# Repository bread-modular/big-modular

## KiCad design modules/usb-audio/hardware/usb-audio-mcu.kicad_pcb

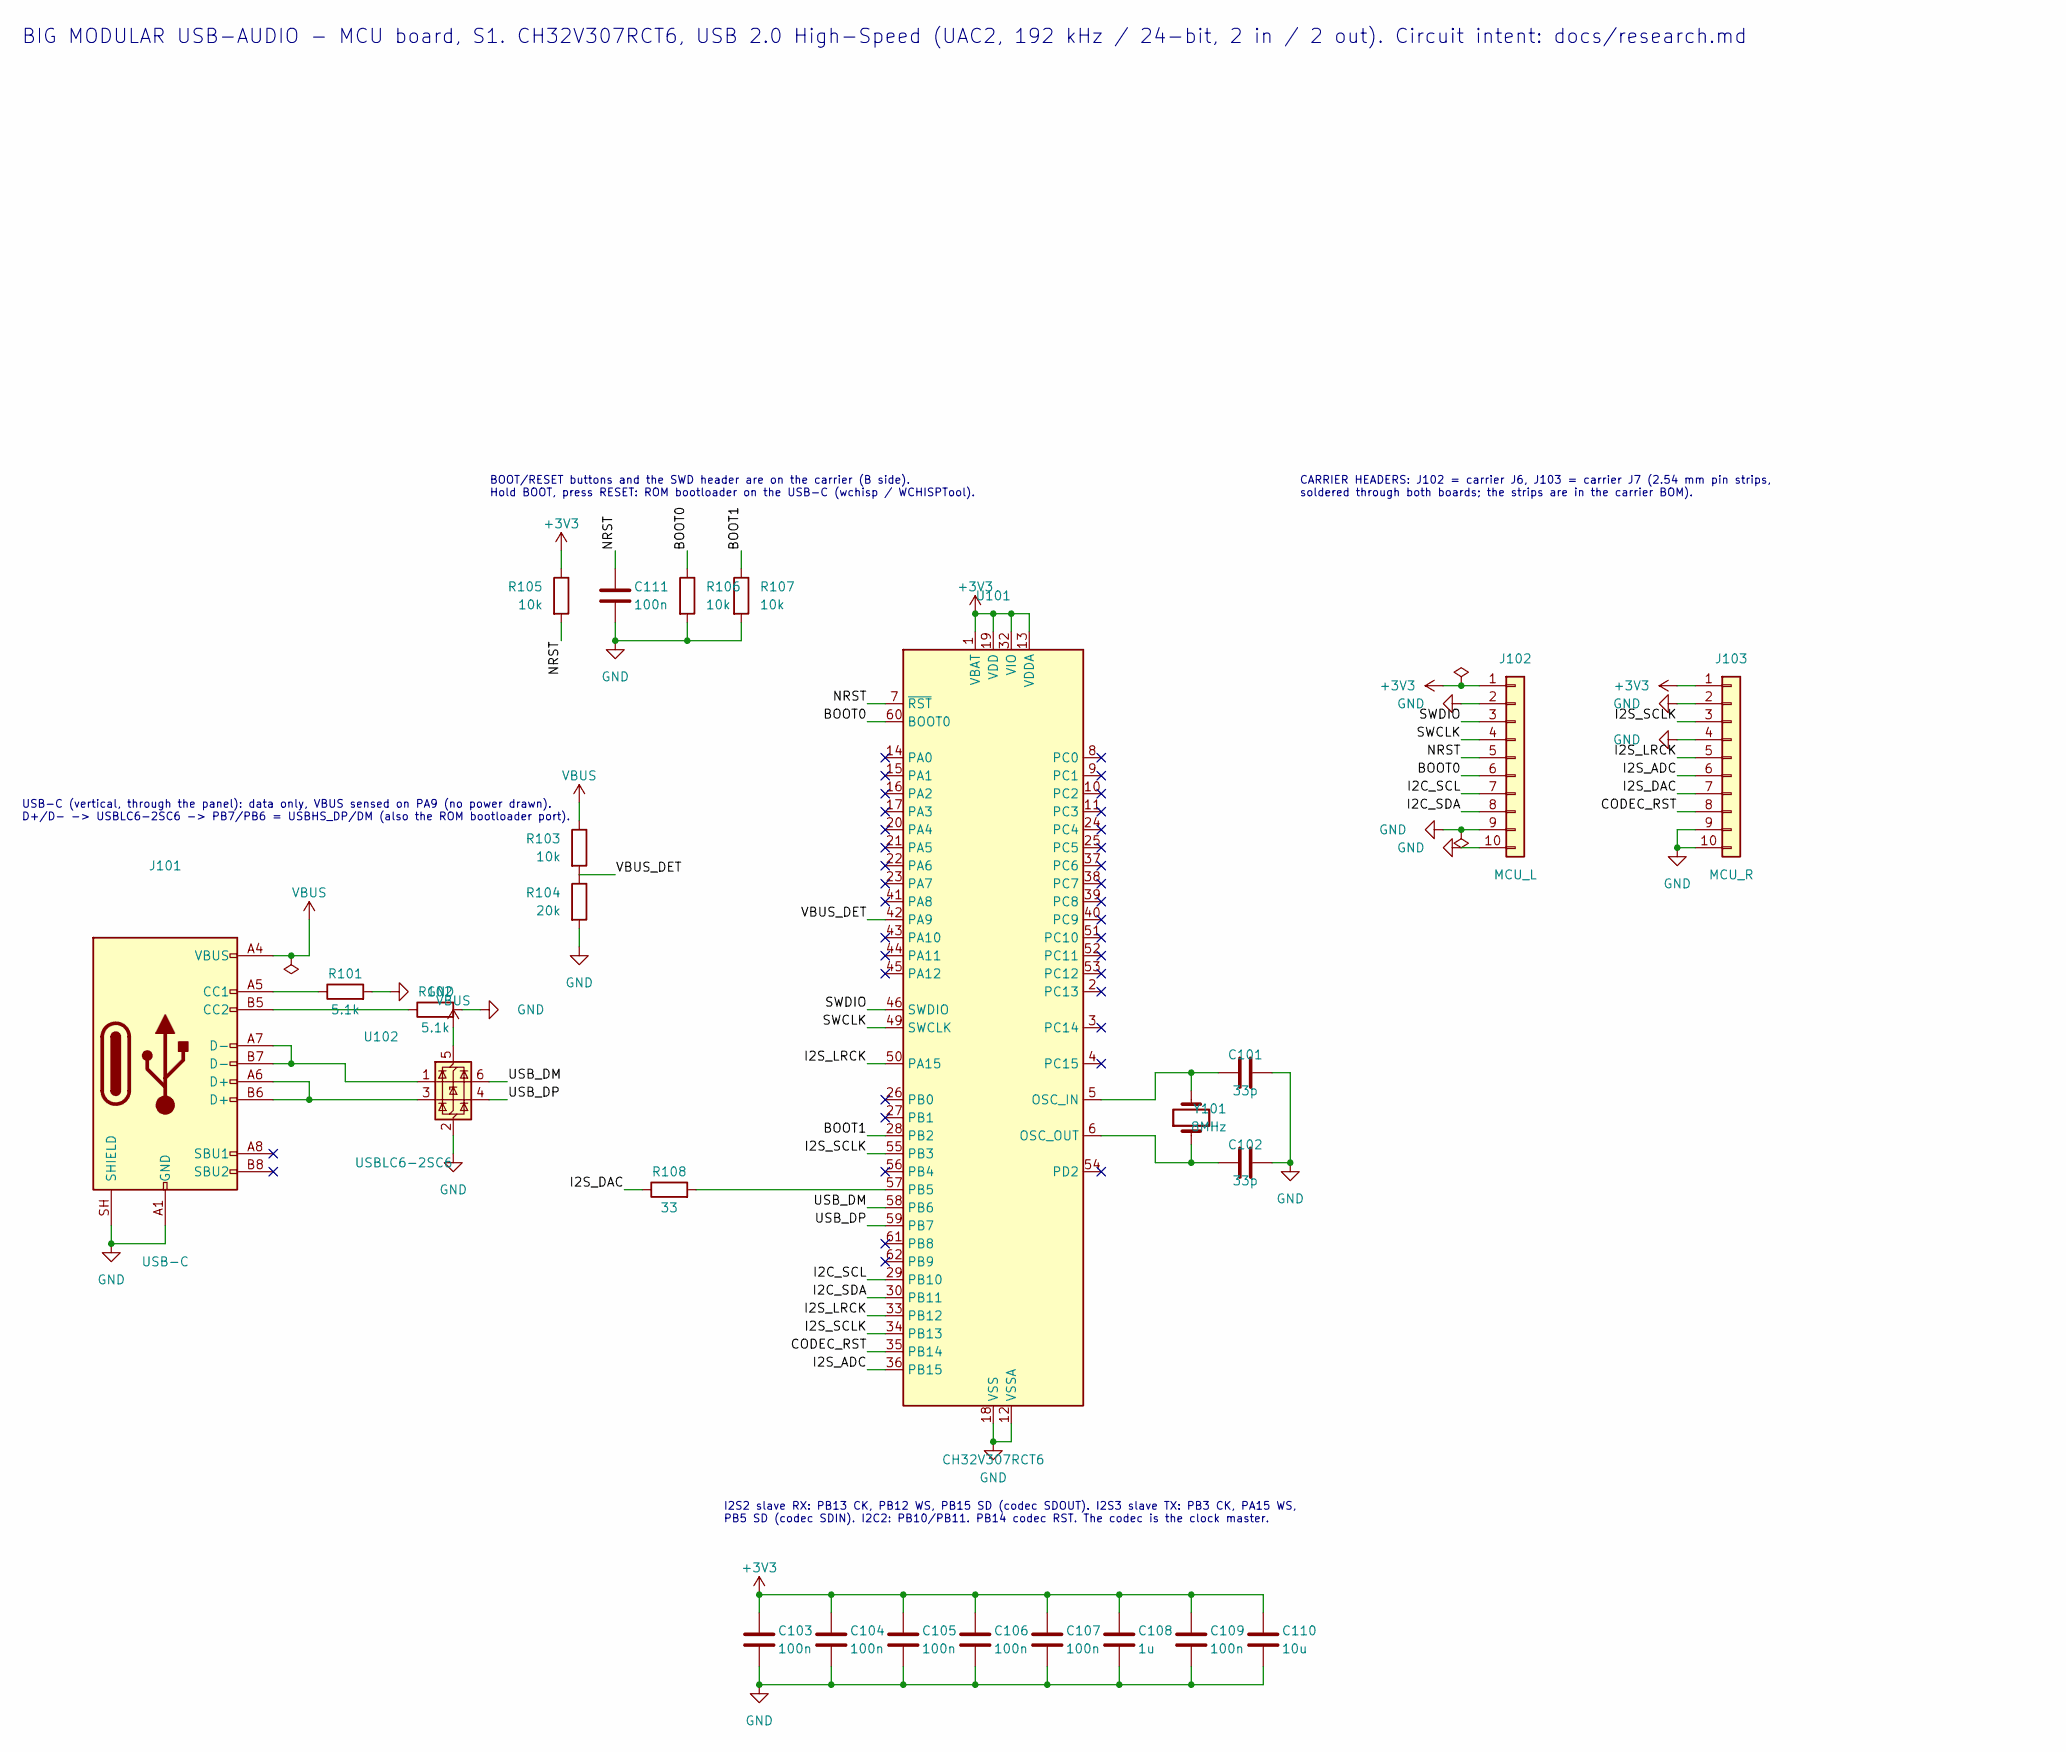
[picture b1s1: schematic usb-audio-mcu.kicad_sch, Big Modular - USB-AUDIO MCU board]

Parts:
C101, C102: 33p; C_0402_1005Metric; Voltage 50V; MPN 0402CG330J500NT; LCSC C1562
C103, C104, C105, C106, C107, C109, C111: 100n; C_0402_1005Metric; Voltage 16V; MPN CL05B104KO5NNNC; LCSC C1525
C108: 1u; C_0402_1005Metric; Voltage 25V; MPN CL05A105KA5NQNC; LCSC C52923
C110: 10u; C_0603_1608Metric; Voltage 10V; MPN CL10A106KP8NNNC; LCSC C19702
J101: USB-C; USB_C_Receptacle_HRO_TYPE-C-31-D-15_Vertical; MPN TYPE-C-31-D-15; LCSC C22464480
J102: MCU_L; PinHeader_1x10_P2.54mm_Vertical
J103: MCU_R; PinHeader_1x10_P2.54mm_Vertical
R101, R102: 5.1k; R_0402_1005Metric; MPN 0402WGF5101TCE; LCSC C25905
R103, R105, R106, R107: 10k; R_0402_1005Metric; MPN 0402WGF1002TCE; LCSC C25744
R104: 20k; R_0402_1005Metric; MPN 0402WGF2002TCE; LCSC C25765
R108: 33; R_0402_1005Metric; MPN 0402WGF330JTCE; LCSC C25105
U101: CH32V307RCT6; LQFP-64_10x10mm_P0.5mm; MPN CH32V307RCT6; LCSC C2988083
U102: USBLC6-2SC6; SOT-23-6; MPN USBLC6-2SC6; LCSC C7519
Y101: 8MHz; Crystal_SMD_5032-2Pin_5.0x3.2mm; MPN X50328MSB2GI; LCSC C115962

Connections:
+3V3: C103.1, C104.1, C105.1, C106.1, C107.1, C108.1, C109.1, C110.1, J102.1, J103.1, R105.1, U101.1 (VBAT), U101.13 (VDDA), U101.19 (VDD), U101.32 (VIO), U101.48 (VDD), U101.64 (VIO)
/BOOT0: J102.6, R106.1, U101.60 (BOOT0)
/BOOT1: R107.1, U101.28 (PB2)
/CODEC_RST: J103.8, U101.35 (PB14)
/I2C_SCL: J102.7, U101.29 (PB10)
/I2C_SDA: J102.8, U101.30 (PB11)
/I2S_ADC: J103.6, U101.36 (PB15)
/I2S_DAC: J103.7, R108.1
/I2S_LRCK: J103.5, U101.33 (PB12), U101.50 (PA15)
/I2S_SCLK: J103.3, U101.34 (PB13), U101.55 (PB3)
/NRST: C111.1, J102.5, R105.2, U101.7 (~RST)
/SWCLK: J102.4, U101.49 (SWCLK)
/SWDIO: J102.3, U101.46 (SWDIO)
/USB_DM: U101.58 (PB6), U102.6 (I/O1)
/USB_DP: U101.59 (PB7), U102.4 (I/O2)
/VBUS_DET: R103.2, R104.1, U101.42 (PA9)
GND: C101.2, C102.2, C103.2, C104.2, C105.2, C106.2, C107.2, C108.2, C109.2, C110.2, C111.2, J101.A1 (GND), J101.A12 (GND), J101.B1 (GND), J101.B12 (GND), J101.SH (SHIELD), J102.2, J102.9, J102.10, J103.2, J103.4, J103.9, J103.10, R101.2, R102.2, R104.2, R106.2, R107.2, U101.12 (VSSA), U101.18 (VSS), U101.31 (VSS), U101.47 (VSS), U101.63 (VSS), U102.2 (GND)
unnamed: J101.A5 (CC1), R101.1
unnamed: J101.B5 (CC2), R102.1
unnamed: J101.A6 (D+), J101.B6 (D+), U102.3 (I/O2)
unnamed: J101.A7 (D-), J101.B7 (D-), U102.1 (I/O1)
unnamed: C101.1, U101.5 (OSC_IN), Y101.2
unnamed: C102.1, U101.6 (OSC_OUT), Y101.1
unnamed: R108.2, U101.57 (PB5)
VBUS: J101.A4 (VBUS), J101.A9 (VBUS), J101.B4 (VBUS), J101.B9 (VBUS), R103.1, U102.5 (VBUS)

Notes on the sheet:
BIG MODULAR USB-AUDIO - MCU board, S1. CH32V307RCT6, USB 2.0 High-Speed (UAC2, 192 kHz / 24-bit, 2 in / 2 out). Circuit intent: docs/research.md
CARRIER HEADERS: J102 = carrier J6, J103 = carrier J7 (2.54 mm pin strips, soldered through both boards; the strips are in the carrier BOM).
BOOT/RESET buttons and the SWD header are on the carrier (B side). Hold BOOT, press RESET: ROM bootloader on the USB-C (wchisp / WCHISPTool).
I2S2 slave RX: PB13 CK, PB12 WS, PB15 SD (codec SDOUT). I2S3 slave TX: PB3 CK, PA15 WS, PB5 SD (codec SDIN). I2C2: PB10/PB11. PB14 codec RST. The codec is the clock master.
USB-C (vertical, through the panel): data only, VBUS sensed on PA9 (no power drawn). D+/D- -> USBLC6-2SC6 -> PB7/PB6 = USBHS_DP/DM (also the ROM bootloader port).

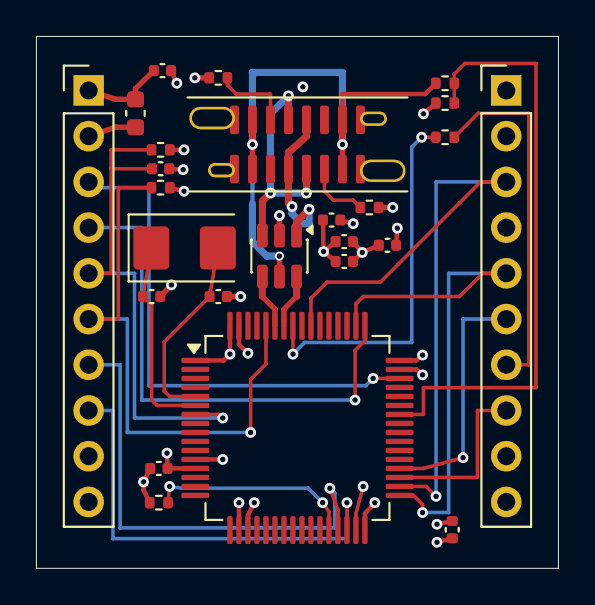
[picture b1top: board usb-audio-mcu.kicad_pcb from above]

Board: 4 copper layers, 29.0 x 29.5 mm, 25 parts (0 on the bottom side), 25 nets.

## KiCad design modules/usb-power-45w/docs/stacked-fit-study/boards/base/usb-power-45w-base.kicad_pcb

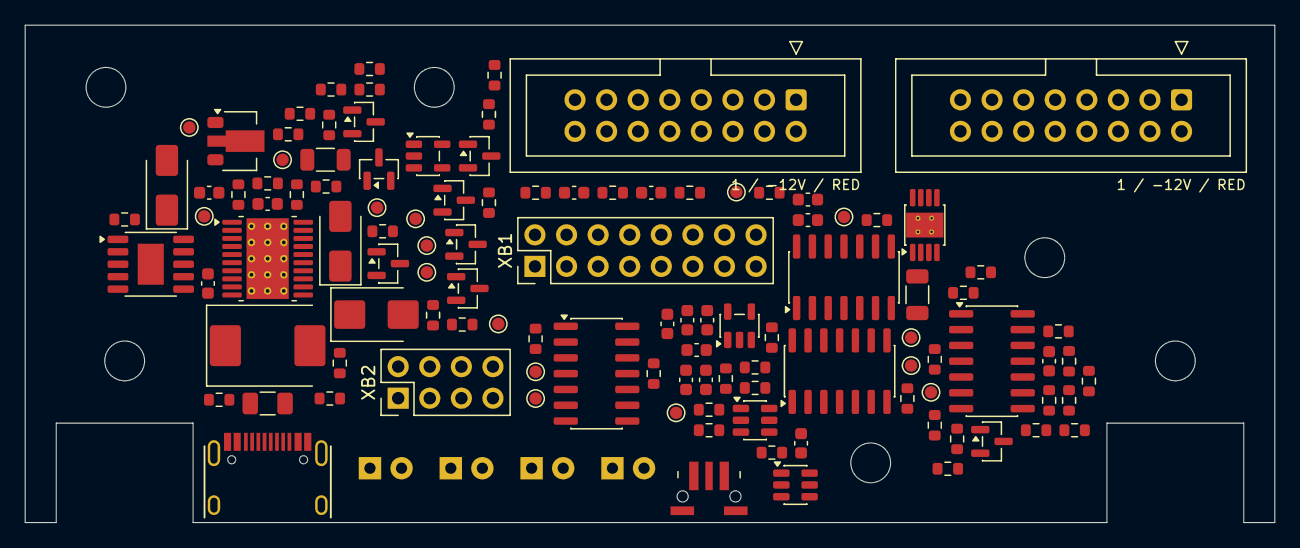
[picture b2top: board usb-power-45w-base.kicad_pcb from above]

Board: 4 copper layers, 100.5 x 40.0 mm, 120 parts (0 on the bottom side), 65 nets, no tracks yet.

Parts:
C1, C2, C46, C49: 1u; C_0603_1608Metric
C3: 22n; C_0603_1608Metric
C47: 10u; C_1206_3216Metric
C48, C50, C51, C52, C53, C54, C55, C56, C57, C58: 100n; C_0603_1608Metric
D1: SMBJ22A; D_SMB
D8: MAIN LED; LED_D3.0mm_Horizontal_O1.27mm_Z2.0mm_Edge
D9: SMAZ24-13-F; D_SMA
D10: SS1060; D_SMC
D11: SS34; D_SMA
D15: BAT54SLT1G; SOT-23
D16: +12V LED; LED_D3.0mm_Horizontal_O1.27mm_Z2.0mm_Edge
D17: +5V LED; LED_D3.0mm_Horizontal_O1.27mm_Z2.0mm_Edge
D18: -12V LED; LED_D3.0mm_Horizontal_O1.27mm_Z2.0mm_Edge
F1: 5A 63V; Fuse_1206_3216Metric
J1: TYPE-C-31-M-12; HRO-TYPE-C-31-M-12
J2, J3: IDC 2x8 box header; IDC-Header_2x08_P2.54mm_Vertical
MHB1, MHB2, MHB3, MHB4: M3 x 5.0 F-F hex standoff (study); MountingHole_3.2mm_M3
Q2: BCX53-16,115; SOT-89-3
Q3: MMBT3906; SOT-23
Q5, Q6, Q7, Q8, Q9, Q10: 2N7002; SOT-23
R1, R4, R75: 120k; R_0603_1608Metric
R2, R37, R46, R62, R80: 100k; R_0603_1608Metric
R3: 7.5k; R_0603_1608Metric
R5, R73: 3.3k; R_0603_1608Metric
R22, R29, R59, R60, R74, R86, R87, R88: 1k; R_0603_1608Metric
R23: 33; R_0603_1608Metric
R24: 6.8k; R_0603_1608Metric
R26: 20k; R_0603_1608Metric
R27: 10k; R_1206_3216Metric
R28, R35, R36, R44, R45, R58, R63, R64, R66, R67, R68, R70, R71, R72, R76, R79, R81, R84, R85: 10k; R_0603_1608Metric
R65: 47k; R_0603_1608Metric
R69, R77: 33k; R_0603_1608Metric
R78: 12k; R_0603_1608Metric
R82: 470k; R_0603_1608Metric
R83: 220k; R_0603_1608Metric
R91: 15k; R_0603_1608Metric
SW1: TL3340AF160QG; SW_TL3340AF160QG_HandSolder
TP1: VPD; TestPoint_Pad_D1.0mm
TP2: VPD_U1; TestPoint_Pad_D1.0mm
TP3: EF_IN; TestPoint_Pad_D1.0mm
TP4: VIN; TestPoint_Pad_D1.0mm
TP5: MAIN_OK; TestPoint_Pad_D1.0mm
TP6, TP11: FAULT_LATCH; TestPoint_Pad_D1.0mm
TP7: EF_IMON; TestPoint_Pad_D1.0mm
TP8: GND; TestPoint_Pad_D1.0mm
TP9: RUN; TestPoint_Pad_D1.0mm
TP10: ARMED; TestPoint_Pad_D1.0mm
TP12: P12_OK; TestPoint_Pad_D1.0mm
TP13: P5_OK; TestPoint_Pad_D1.0mm
TP14: N12_OK; TestPoint_Pad_D1.0mm
TP15: V20_OK; TestPoint_Pad_D1.0mm
TP16: V3V3; TestPoint_Pad_D1.0mm
U1: CH224A; SSOP-10-1EP_3.9x4.9mm_P1mm_EP2.1x3.3mm
U5: TPS16630PWPR; HTSSOP-20-1EP_4.4x6.5mm_P0.65mm_EP3.4x6.5mm_Mask2.96x2.96mm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
U9: TPS7A1633DGNR; TPS7A16_DGN0008C
U10, U11: TPS3808G01DBVR; SOT-23-6
U12: SN74HC74DR; SOIC-14_3.9x8.7mm_P1.27mm
U13: SN74HC08DR; SOIC-14_3.9x8.7mm_P1.27mm
U14: SN74HC20DR; SOIC-14_3.9x8.7mm_P1.27mm
U15, U19: SN74LVC1G17DBVR; SOT-23-5
U18: LM2901DR; SOIC-14_3.9x8.7mm_P1.27mm
XB1: PinHeader_2x08_P2.54mm_Vertical (study interconne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; PinHeader_2x08_P2.54mm_Vertical
XB2: PinHeader_2x04_P2.54mm_Vertical (study interconne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; PinHeader_2x04_P2.54mm_Vertical

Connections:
+5V: J2.11, J2.12, J3.11, J3.12, R45.1, R77.1, XB1.11, XB1.12
+12V: J2.9, J2.10, J3.9, J3.10, R36.1, R75.1, XB1.9, XB1.10
-12V: J2.1, J2.2, J3.1, J3.2, R58.2, R82.2, XB1.15, XB1.16
/Always-on control - all-rail fault latch and RESET/ANY_BAD: R72.1, U14.6
/Always-on control - all-rail fault latch and RESET/ARMED: TP10.1, U12.5, U13.4
/Always-on control - all-rail fault latch and RESET/BAD_FILTERED: U13.5, U15.4
/Always-on control - all-rail fault latch and RESET/BAD_RC: C51.1, R72.2, U15.2
/Always-on control - all-rail fault latch and RESET/FAULT_CLK: U12.11, U13.6
/Always-on control - all-rail fault latch and RESET/FAULT_LATCH: TP6.1, TP11.1, U12.9
/Always-on control - all-rail fault latch and RESET/NOT_FAULT: U12.8, U13.2
/Always-on control - all-rail fault latch and RESET/POR_SENSE: R65.2, R66.1, U10.5
/Always-on control - all-rail fault latch and RESET/POR_SER: R65.1, R91.2
/Always-on control - all-rail fault latch and RESET/RESET_BTN_N: R68.2, SW1.1, SW1.3, U10.3
/Always-on control - all-rail fault latch and RESET/RESET_N: R67.2, U10.1, U11.3, U12.1, U12.13, U13.1
/Always-on control - all-rail fault latch and RESET/START_CT: C49.1, U11.4
/Always-on control - all-rail fault latch and RESET/START_READY: R71.2, U11.1, U12.3
/Always-on control - all-rail fault latch and RESET/START_SENSE: R69.2, R70.1, U11.5
/Always-on control - all-rail fault latch and RESET/TIMER_GO: R69.1, U13.8
/MAIN_LED_OK: Q6.1, U13.11, U14.1
/MAIN_OK: R63.2, TP5.1, U5.15, U5.16, U13.12, XB2.2
/N12_OK: Q9.1, TP14.1, U14.5, U19.4
/N12_STATUS: R62.2, U18.14, U19.2, XB2.6
/NOT_RUN: Q5.1, U14.8
/Negative rail protection and level shifting/NEG_OFF_K: Q5.3, XB2.8
/Negative rail protection and level shifting/NEG_OFF_LED: R59.2, R60.2, XB2.7
/P5_OK: Q8.1, R44.2, TP13.1, U14.4, U18.2, XB2.5
/P12_OK: Q7.1, R35.2, TP12.1, U14.2, U18.1, XB2.4
/Protected outputs - voltage monitors and panel LEDs/LED_RETURN: Q6.2, Q7.2, Q8.2, Q9.2, Q10.3
/Protected outputs - voltage monitors and panel LEDs/MON_20: R83.2, R84.1, U18.11
/Protected outputs - voltage monitors and panel LEDs/MON_N12: D15.3, R81.2, R82.1, U18.8
/Protected outputs - voltage monitors and panel LEDs/MON_N_SER: R80.2, R81.1
/Protected outputs - voltage monitors and panel LEDs/MON_P5: R78.2, R79.1, U18.5
/Protected outputs - voltage monitors and panel LEDs/MON_P5_SER: R77.2, R78.1
/Protected outputs - voltage monitors and panel LEDs/MON_P12: R75.2, R76.1, U18.7
/Protected outputs - voltage monitors and panel LEDs/REF_GOOD: C56.1, R73.2, R74.1, U18.4, U18.6, U18.9, U18.10
/RUN: Q10.1, R37.1, R46.1, R64.1, TP9.1, U5.13, U13.3, U13.9, U14.9, U14.10, U14.12, U14.13, XB2.3
/USB PD and main eFuse/CC1: J1.A5, U1.7
/USB PD and main eFuse/CC2: J1.B5, U1.6
/USB PD and main eFuse/EF_DVDT: C3.1, U5.10
/USB PD and main eFuse/EF_ILM: R5.1, U5.11
/USB PD and main eFuse/EF_IMON: R26.1, TP7.1, U5.14
/USB PD and main eFuse/EF_IN: C2.1, D10.1, TP3.1, U5.1, U5.2, U5.3, U5.6
/USB PD and main eFuse/EF_OV: R4.2, R24.1, U5.8
/USB PD and main eFuse/EF_UV: R2.2, R3.1, U5.7
/USB PD and main eFuse/PD_BASE: Q2.3, Q3.3, R27.1
/USB PD and main eFuse/PD_SENSE: Q2.1, Q3.1, R23.2
/USB PD and main eFuse/VBUS: F1.1, J1.A4, J1.A9
/USB PD and main eFuse/VPD_U1: C1.1, D9.1, D11.2, Q2.2, TP2.1, U1.1, U1.8
/V20_OK: R85.2, TP15.1, U13.10, U13.13, U18.13
/VPD: C46.1, D1.1, D10.2, D11.1, F1.2, Q3.2, R2.1, R23.1, R28.1, R83.1, TP1.1, U9.5, U9.8
GND: C1.2, C2.2, C3.2, C46.2, C47.2, C48.2, C49.2, C50.2, C51.2, C52.2, C53.2, C54.2, C55.2, C56.2, C57.2, C58.2, D1.2, D9.2, D15.1, J1.A1, J1.A12, J1.S1, J2.3, J2.4, J2.5, J2.6, J2.7, J2.8, J3.3, J3.4, J3.5, J3.6, J3.7, J3.8, Q5.2, Q10.2, R1.2, R3.2, R24.2, R26.2, R27.2, R29.2, R36.2, R37.2, R45.2, R46.2, R58.1, R64.2, R66.2, R70.2, R74.2, R76.2, R79.2, R84.2, SW1.2, TP8.1, U1.11, U5.9, U5.12, U5.21, U9.4, U9.9, U10.2, U11.2, U12.7, U13.7, U14.7, U15.3, U18.12, U19.3, XB1.1, XB1.2, XB1.7, XB1.8, XB1.13, XB1.14, XB2.1
unnamed: D8.2, R22.2
unnamed: D8.1, Q6.3
unnamed: D16.2, R86.2
unnamed: D16.1, Q7.3
unnamed: D17.2, R87.2
unnamed: D17.1, Q8.3
unnamed: D18.2, R88.2
unnamed: D18.1, Q9.3
unnamed: R4.1, R28.2
unnamed: R5.2, R29.1
unnamed: R1.1, U1.9
unnamed: U1.4, U1.5
V3V3: C47.1, C48.1, C50.1, C52.1, C53.1, C54.1, C55.1, C57.1, C58.1, D15.2, R22.1, R35.1, R44.1, R59.1, R60.1, R62.1, R63.1, R67.1, R68.1, R71.1, R73.1, R80.1, R85.1, R86.1, R87.1, R88.1, R91.1, TP16.1, U9.1, U10.6, U11.6, U12.2, U12.4, U12.10, U12.12, U12.14, U13.14, U14.14, U15.5, U18.3, U19.5
VIN: TP4.1, U5.18, U5.19, U5.20, XB1.3, XB1.4, XB1.5, XB1.6

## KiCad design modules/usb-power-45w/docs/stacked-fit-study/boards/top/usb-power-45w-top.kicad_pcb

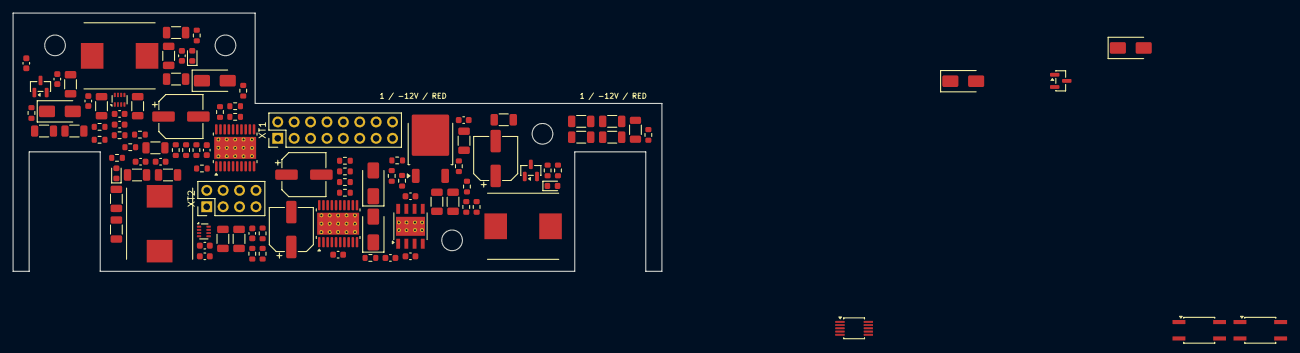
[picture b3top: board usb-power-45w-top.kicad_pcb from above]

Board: 4 copper layers, 100.5 x 40.0 mm, 109 parts (0 on the bottom side), 54 nets, no tracks yet.

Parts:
C5: 47u; CP_Elec_6.3x7.7
C6, C7, C15, C16, C24, C25, C26: 10u; C_1206_3216Metric
C8, C10, C17, C19, C27, C28, C37, C39, C40, C42: 100n; C_0603_1608Metric
C9, C18: 22n; C_0603_1608Metric
C11, C12, C13, C14, C20, C21, C22, C23, C29, C30, C31, C32, C33: 22u; C_1206_3216Metric
C34, C35, C36: 100u; CP_Elec_6.3x7.7
C38, C41, C43, C44, C45: 1u; C_0603_1608Metric
D2, D3, D4, D12, D13, D14: SS34; D_SMA
D5, D6, D7: RED; LED_0603_1608Metric
D19, D20: BAT54SLT1G; SOT-23
L1: 6.8u; L_SLO1040H6R8MTT
L2: 3.3u; L_SLO1040H6R8MTT
L3: 15u; L_SLO1040H6R8MTT
MHT1, MHT2, MHT3, MHT4: M3 x 5.0 F-F hex standoff (study); MountingHole_3.2mm_M3
Q1: MMBT3906; SOT-23
Q4: FQD13N06LTM; TO-252-2
R8, R54: 47k; R_0603_1608Metric
R9: 3.3k; R_0603_1608Metric
R10, R19, R21, R33, R38, R55, R61, R90: 10k; R_0603_1608Metric
R11, R52: 68k; R_0603_1608Metric
R12, R31: 13k; R_0603_1608Metric
R13, R39, R41, R53: 33k; R_0603_1608Metric
R14, R16, R17, R30, R32, R57: 100k; R_0603_1608Metric
R15, R42: 9.1k; R_0603_1608Metric
R18: 20k; R_0603_1608Metric
R20: 1k; R_0603_1608Metric
R34, R43: 6.8k; R_0603_1608Metric
R40: 12k; R_0603_1608Metric
R48, R49: 0.1; R_1206_3216Metric
R50, R51: 10k; R_1206_3216Metric
R56: 22k; R_0603_1608Metric
R89: 33; R_0603_1608Metric
U2, U3: TPS62933FDRLR; SOT-583-8
U4: LMR38020FDDAR; TI_SO-PowerPAD-8_ThermalVias
U6, U7: TPS16630PWPR; HTSSOP-20-1EP_4.4x6.5mm_P0.65mm_EP3.4x6.5mm_Mask2.96x2.96mm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
U8: LM5067MM-2/NOPB; MSOP-10_3x3mm_P0.5mm
U16, U17: LTV-354T; SO-4_4.4x3.6mm_P2.54mm
XT1: PinHeader_2x08_P2.54mm_Vertical (study interconne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; PinHeader_2x08_P2.54mm_Vertical
XT2: PinHeader_2x04_P2.54mm_Vertical (study interconne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; PinHeader_2x04_P2.54mm_Vertical

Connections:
+5V: C41.1, D13.1, U7.18, U7.19, U7.20, XT1.11, XT1.12
+12V: C38.1, D12.1, U6.18, U6.19, U6.20, XT1.9, XT1.10
-12V: C45.2, D14.2, Q4.2, R90.1, XT1.15, XT1.16
/+5 V converter and output eFuse/P5_DVDT: C40.1, U7.10
/+5 V converter and output eFuse/P5_ILIM: R43.1, U7.11
/+5 V converter and output eFuse/P5_OV: R41.2, R42.1, U7.8
/+5 V converter and output eFuse/P5_UV: R39.2, R40.1, U7.7
/+12 V converter and output eFuse/P12_DVDT: C37.1, U6.10
/+12 V converter and output eFuse/P12_ILIM: R34.1, U6.11
/+12 V converter and output eFuse/P12_OV: R32.2, R33.1, U6.8
/+12 V converter and output eFuse/P12_OV_SER: R32.1, R38.2
/+12 V converter and output eFuse/P12_UV: R30.2, R31.1, U6.7
/MAIN_OK: U2.2, U3.2, XT2.2
/N12_STATUS: U17.4, XT2.6
/Negative converter - raw rail/EN_N: R17.2, R18.1, U4.2
/Negative converter - raw rail/FB_N: R14.1, R15.1, U4.5
/Negative rail protection and level shifting/NEG_OFF_K: U16.2, XT2.8
/Negative rail protection and level shifting/NEG_OFF_LED: U16.1, XT2.7
/Negative rail protection and level shifting/N_GATE: Q4.1, R57.1, U8.8
/Negative rail protection and level shifting/N_OUT_PIN: D20.2, D20.3, R90.2, U8.9
/Negative rail protection and level shifting/N_OV: R54.2, R55.1, U8.3
/Negative rail protection and level shifting/N_PGD: U8.10, U17.2
/Negative rail protection and level shifting/N_PGD_LED: R61.2, U17.1
/Negative rail protection and level shifting/N_PWR: R56.1, U8.4
/Negative rail protection and level shifting/N_SENSE: Q4.3, R48.1, R49.1, R57.2, R89.1
/Negative rail protection and level shifting/N_SENSE_PIN: D19.2, D19.3, R89.2, U8.7
/Negative rail protection and level shifting/N_TIMER: C44.1, U8.6
/Negative rail protection and level shifting/N_UV: R52.2, R53.1, U8.2, U16.4
/Negative rail protection and level shifting/N_VCC: C43.1, R50.2, R51.2, U8.1
/P5_OK: U7.15, U7.16, XT2.5
/P12_OK: U6.15, U6.16, XT2.4
/RUN: U6.13, U7.13, XT2.3
GND: C5.2, C6.2, C7.2, C8.2, C9.2, C11.2, C12.2, C13.2, C14.2, C15.2, C16.2, C17.2, C18.2, C20.2, C21.2, C22.2, C23.2, C24.2, C29.2, C30.2, C31.2, C32.2, C33.2, C34.2, C35.2, C36.1, C37.2, C38.2, C39.2, C40.2, C41.2, C42.2, C45.1, D2.2, D3.2, D4.1, D5.1, D6.1, D7.2, D12.2, D13.2, D14.1, L3.2, R9.2, R10.2, R12.2, R14.2, R16.1, R31.2, R33.2, R34.2, R40.2, R42.2, R43.2, R52.1, R54.1, R61.1, U2.1, U2.4, U3.4, U6.9, U6.21, U7.9, U7.21, U17.3, XT1.1, XT1.2, XT1.7, XT1.8, XT1.13, XT1.14, XT2.1
N12_RAW: C25.2, C26.2, C27.2, C29.1, C30.1, C31.1, C32.1, C33.1, C36.2, C43.2, C44.2, D4.2, D19.1, D20.1, R13.1, R15.2, R18.2, R21.2, R48.2, R49.2, R53.2, R55.2, R56.2, U4.1, U4.9, U8.5, U16.3
unnamed: D5.2, R19.2
unnamed: D6.2, R20.2
unnamed: D7.1, R21.1
unnamed: Q1.1, R16.2
unnamed: Q1.3, R17.1
unnamed: C10.1, U2.6
unnamed: R8.1, R9.1, U2.8
unnamed: C9.1, U2.7
unnamed: C10.2, L1.1, U2.5
unnamed: C19.1, U3.6
unnamed: R11.1, R12.1, U3.8
unnamed: R10.1, U3.1
unnamed: C18.1, U3.7
unnamed: C19.2, L2.1, U3.5
unnamed: C28.2, U4.7
unnamed: R13.2, U4.4
unnamed: C28.1, L3.1, U4.8
P5_RAW: C20.1, C21.1, C22.1, C23.1, C35.1, C42.1, D3.1, L2.2, R11.2, R20.1, R39.1, R41.1, U7.1, U7.2, U7.3, U7.6
P12_RAW: C11.1, C12.1, C13.1, C14.1, C34.1, C39.1, D2.1, L1.2, Q1.2, R8.2, R19.1, R30.1, R38.1, U6.1, U6.2, U6.3, U6.6
VIN: C5.1, C6.1, C7.1, C8.1, C15.1, C16.1, C17.1, C24.1, C25.1, C26.1, C27.1, R50.1, R51.1, U2.3, U3.3, U4.3, XT1.3, XT1.4, XT1.5, XT1.6
